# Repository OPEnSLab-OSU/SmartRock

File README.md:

# Smart Rock |<!-- [Updates](https://github.com/OPEnSLab-OSU/OPEnS-Lab-Home/wiki/smart-rock-updates) |--> [Wiki](https://github.com/OPEnSLab-OSU/SmartRock/wiki)
Project Leads: **Tyler Slaght**

Project Members; **Chris Milford**, **Owen Schwab**, **Max Emrich**

<!--Past Team Members **Annika Sundstorm** **Colin Hale-Brown**-->

Interested in the project? Email us at: slaghtt@oregonstate.edu

Smart Rock aims to be a low cost, high accuracy, easy to use in-situ water quality measuring device. Our
goal with Smart Rock is to create an open source, low cost, and technically accessible hydrological sensor
suite. The intended result of this work allows data to be collected throughout a watershed; even in varied
and/or harsh conditions to improve system wide watershed knowledge.
Smart Rock could be used as a learning tool for students, teachers, and other citizen scientists. The
device currently costs ˜$350 in materials and takes approximately 4-8 hours to assemble and program.

Comprehensive Build Guide -> https://github.com/OPEnSLab-OSU/SmartRock/blob/master/Documentation/SmartRock_Guide-compressed.pdf

Smart Rock Paper -> https://github.com/OPEnSLab-OSU/SmartRock/blob/master/Documentation/SmartRock_Paper.pdf

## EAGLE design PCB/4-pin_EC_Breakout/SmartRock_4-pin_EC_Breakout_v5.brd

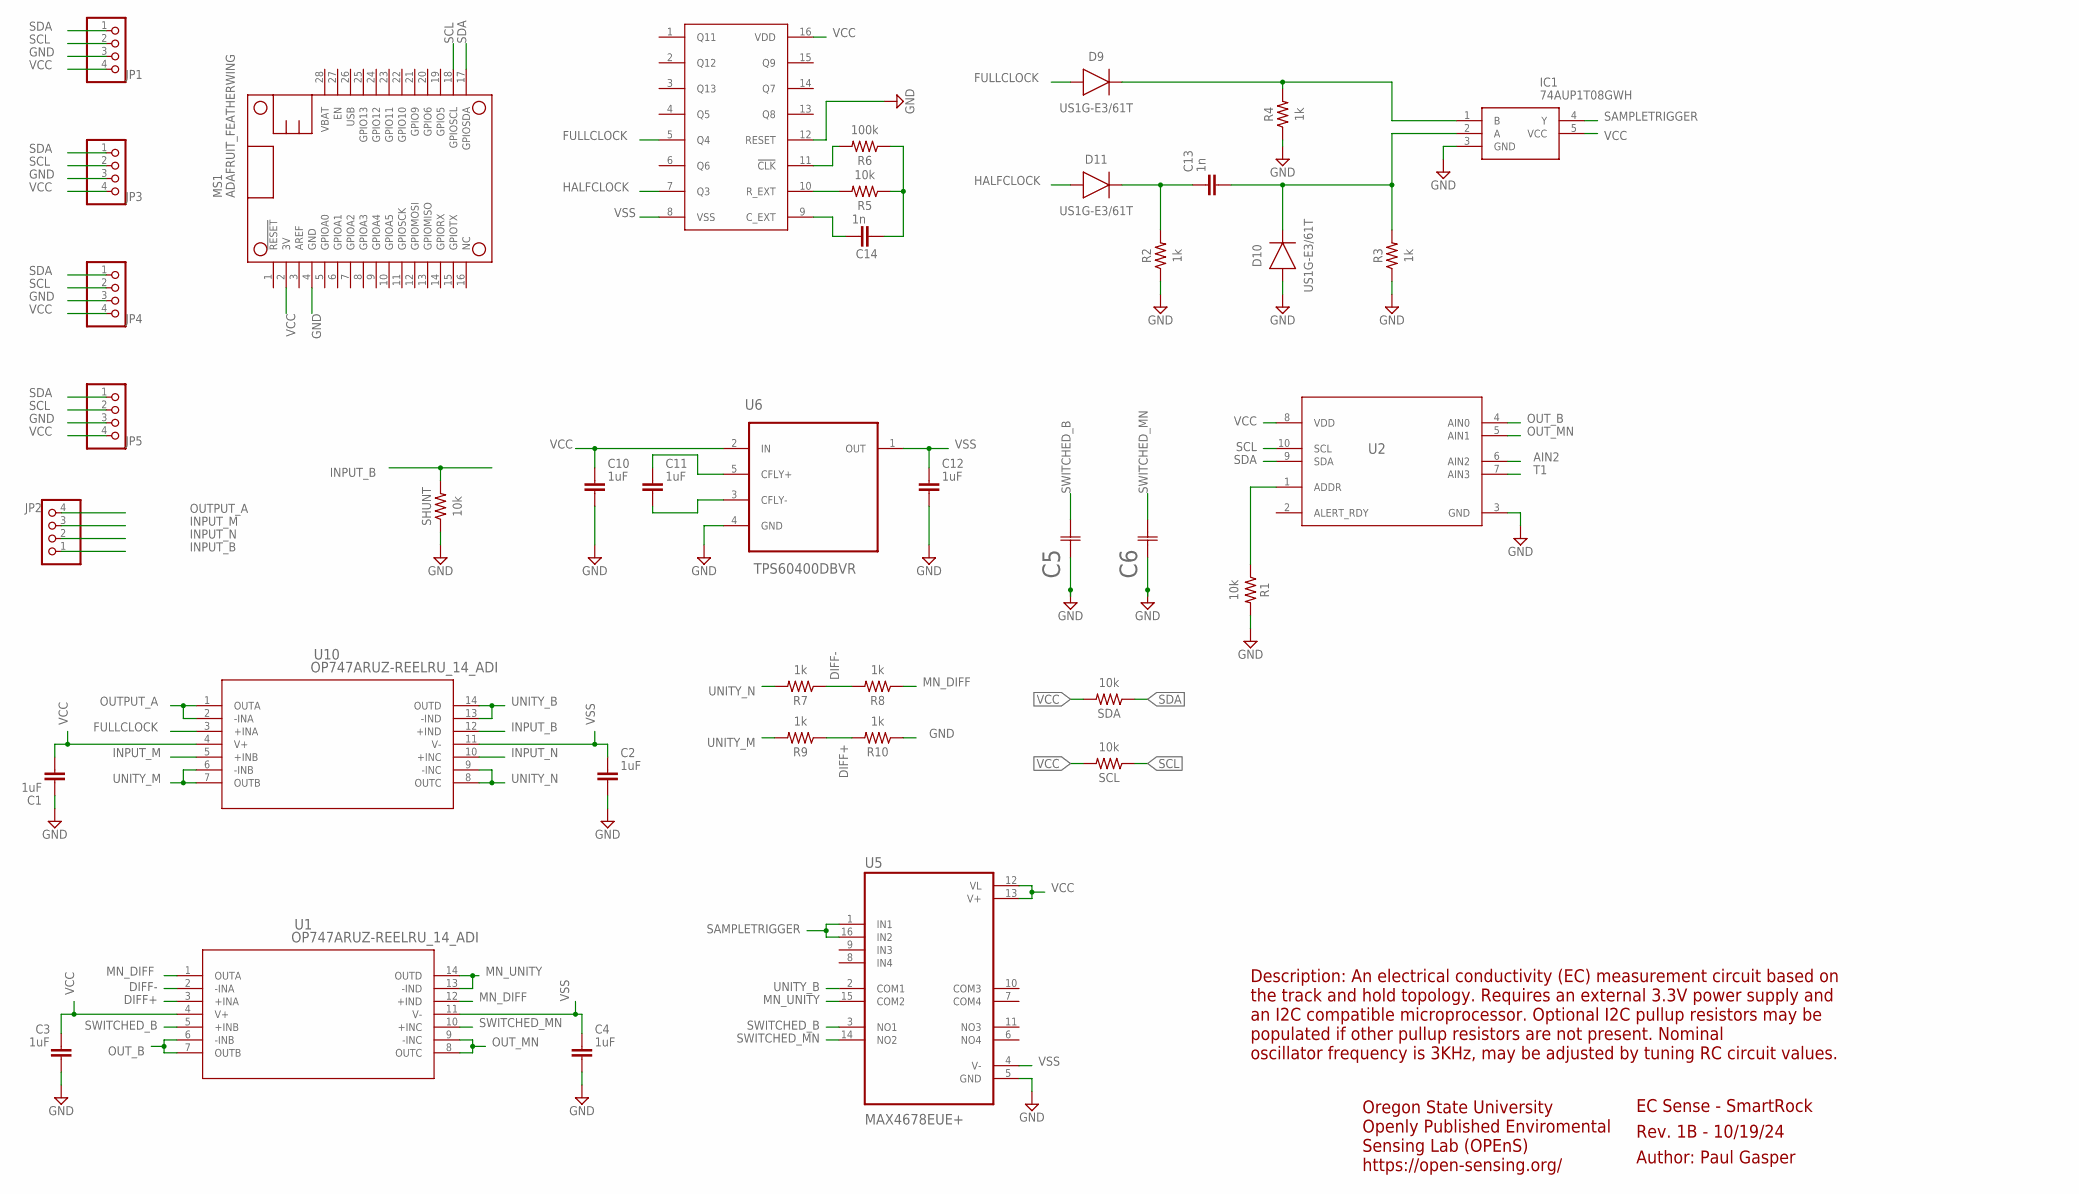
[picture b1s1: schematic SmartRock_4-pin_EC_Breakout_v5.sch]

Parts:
C1, C2, C3, C4, C10, C11, C12: 1uF; CAPC1005X60
C5, C6: 865090640004CAP_WCAP-ASLU_04P0X05P5_WRE-L; CAP_WCAP-ASLU_04P0X05P5_WRE-L
C13, C14: 1n; CAPC1005X60
D9, D10, D11: US1G-E3/61T; DIOM5226X290N
IC1: 74AUP1T08GWH; SOT65P212X110-5N
JP1, JP2, JP3, JP4, JP5: PINHD-1X4; 1X04
MS1: ADAFRUIT_FEATHERWING
R1, R5: 10k; RESC1005X40
R2, R3, R4, R7, R8, R9, R10: 1k; RESC1005X40
R6: 100k; RESC1005X40
SCL: 10k; RESC1005X40
SDA: 10k; RESC1005X40
SHUNT: 10k; RESC1005X40
U1, U10: OP747ARUZ-REELRU_14_ADI; RU_14_ADI
U2: ADS1115IDGSRDGS0010A_L; DGS0010A_L
U4: CD4060BPWR
U5: MAX4678EUE+; SOP65P640X110-16N
U6: TPS60400DBVR; SOT95P280X145-5N

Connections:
AIN2: U2.6 (AIN2)
DIFF+: R9.1, R10.2, U1.3 (+INA)
DIFF-: R7.1, R8.2, U1.2 (-INA)
FULLCLOCK: D9.2 (A), U4.5 (Q4), U10.3 (+INA)
GND: C1.1, C2.2, C3.2, C4.2, C5.1, C6.1, C10.2, C12.2, D10.2 (A), IC1.3 (GND), JP1.3, JP3.3, JP4.3, JP5.3, MS1.4 (GND), R1.2, R2.1, R3.1, R4.1, R10.1, SHUNT.1, U2.3 (GND), U4.12 (RESET), U5.5 (GND), U6.4 (GND)
HALFCLOCK: D11.2 (A), U4.7 (Q3)
INPUT_B: JP2.1, SHUNT.2, U10.12 (+IND)
INPUT_M: JP2.3, U10.5 (+INB)
INPUT_N: JP2.2, U10.10 (+INC)
MN_DIFF: R8.1, U1.1 (OUTA), U1.12 (+IND)
MN_UNITY: U1.13 (-IND), U1.14 (OUTD), U5.15 (COM2)
unnamed: D9.1 (C), IC1.1 (B), R4.2
unnamed: C13.1, D11.1 (C), R2.2
unnamed: C11.2, U6.3 (CFLY-)
unnamed: C11.1, U6.5 (CFLY+)
unnamed: C13.2, D10.1 (C), IC1.2 (A), R3.2
unnamed: R6.2, U4.11 (!CLK)
unnamed: R5.2, U4.10 (R_EXT)
unnamed: C14.1, U4.9 (C_EXT)
unnamed: C14.2, R5.1, R6.1
unnamed: R1.1, U2.1 (ADDR)
OUTPUT_A: JP2.4, U10.1 (OUTA), U10.2 (-INA)
OUT_B: U1.6 (-INB), U1.7 (OUTB), U2.4 (AIN0)
OUT_MN: U1.8 (OUTC), U1.9 (-INC), U2.5 (AIN1)
SAMPLETRIGGER: IC1.4 (Y), U5.1 (IN1), U5.16 (IN2)
SCL: JP1.2, JP3.2, JP4.2, JP5.2, MS1.18 (GPIOSCL), SCL.1, U2.10 (SCL)
SDA: JP1.1, JP3.1, JP4.1, JP5.1, MS1.17 (GPIOSDA), SDA.1, U2.9 (SDA)
SWITCHED_B: C5.2, U1.5 (+INB), U5.3 (NO1)
SWITCHED_MN: C6.2, U1.10 (+INC), U5.14 (NO2)
T1: U2.7 (AIN3)
UNITY_B: U5.2 (COM1), U10.13 (-IND), U10.14 (OUTD)
UNITY_M: R9.2, U10.6 (-INB), U10.7 (OUTB)
UNITY_N: R7.2, U10.8 (OUTC), U10.9 (-INC)
VCC: C1.2, C3.1, C10.1, IC1.5 (VCC), JP1.4, JP3.4, JP4.4, JP5.4, MS1.2 (3V), SCL.2, SDA.2, U1.4 (V+), U2.8 (VDD), U4.16 (VDD), U5.12 (VL), U5.13 (V+), U6.2 (IN), U10.4 (V+)
VSS: C2.1, C4.1, C12.1, U1.11 (V-), U4.8 (VSS), U5.4 (V-), U6.1 (OUT), U10.11 (V-)

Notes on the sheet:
EC Sense - SmartRock
Rev. 1B - 10/19/24
Author: Paul Gasper
Oregon State University Openly Published Enviromental Sensing Lab (OPEnS) https://open-sensing.org/
Description: An electrical conductivity (EC) measurement circuit based on the track and hold topology. Requires an external 3.3V power supply and an I2C compatible microprocessor. Optional I2C pullup resistors may be populated if other pullup resistors are not present. Nominal oscillator frequency 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

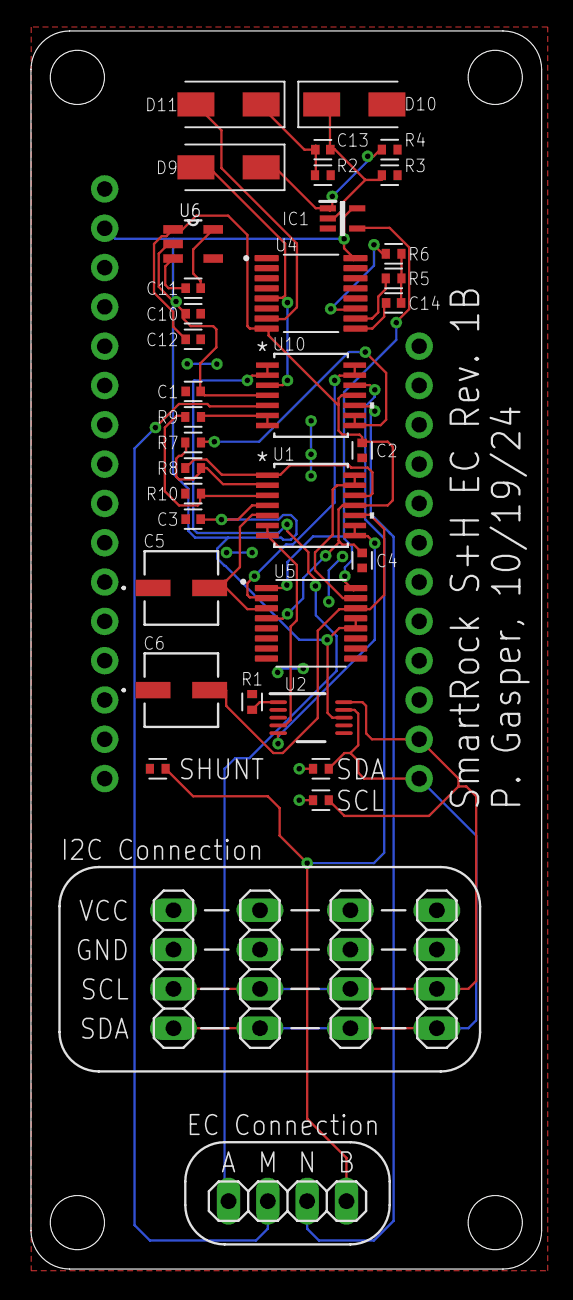
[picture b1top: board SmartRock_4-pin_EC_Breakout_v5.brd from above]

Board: 2 copper layers, 33.0 x 80.0 mm, 40 parts (0 on the bottom side), 33 nets.

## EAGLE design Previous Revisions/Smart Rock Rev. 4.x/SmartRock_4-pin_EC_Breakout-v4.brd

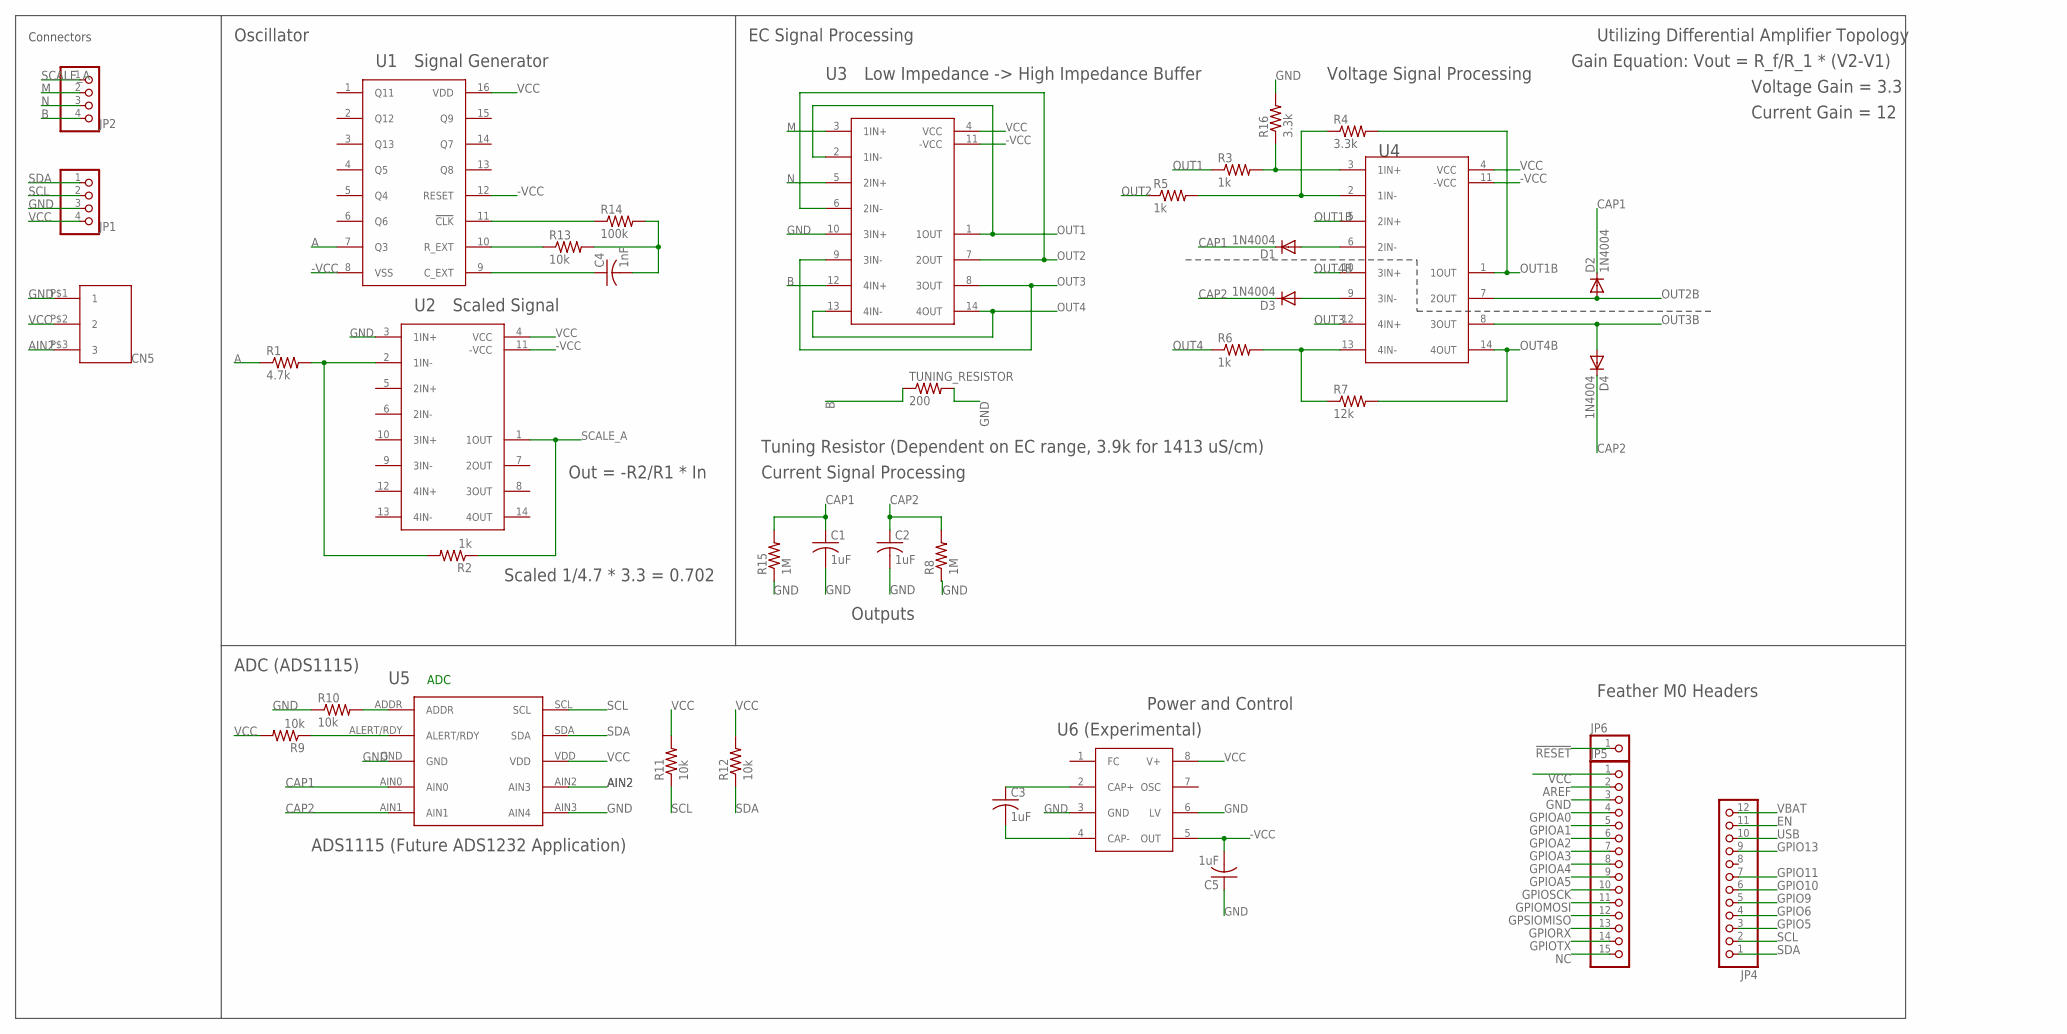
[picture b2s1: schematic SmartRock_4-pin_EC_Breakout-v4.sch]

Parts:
C1, C2, C3, C5: 1uF; C025-024X044
C4: 1nF; C1206
CN2: JST_3PIN_2MM
D1, D2, D3, D4: 1N4004; DO41-10
JP1, JP2: PINHD-1X4; 1X04
JP4: PINHD-1X12-CB; 1X12-CB
JP5: PINHD-1X15-CB; 1X15-CB
JP6: PINHD-1X1CB; 1X01-CLEANBIG
R1: 4.7k; M1206
R2, R3, R5, R6: 1k; M1206
R4, R16: 3.3k; M1206
R7: 12k; M1206
R8, R15: 1M; M1206
R9, R10, R11, R12, R13: 10k; M1206
R14: 100k; M1206
TUNING_RESISTOR: 200; M1206
U1: CD4060BPWR
U2, U3, U4: TL074CPWR; LT074CPWR
U5: ADS1115
U6+: MAX660MX/NOPB

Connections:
!RESET: JP6.1
-VCC: C5.2, U1.8 (VSS), U1.12 (RESET), U2.11 (-VCC), U3.11 (-VCC), U4.11 (-VCC), U6+.5 (OUT)
A: R1.1, U1.7 (Q3)
AIN2: CN2.P$3 (3), U5.AIN2 (AIN3)
AREF: JP5.2
B: JP2.4, TUNING_RESISTOR.1, U3.12 (4IN+)
CAP1: C1.1, D1.C, D2.C, R15.2, U5.AIN0
CAP2: C2.1, D3.C, D4.C, R8.2, U5.AIN1
EN: JP4.11
GND: C1.2, C2.2, C5.1, CN2.P$1 (1), JP1.3, JP5.3, R8.1, R10.1, R15.1, R16.2, TUNING_RESISTOR.2, U2.3 (1IN+), U3.10 (3IN+), U5.AIN3 (AIN4), U5.GND, U6+.3 (GND), U6+.6 (LV)
GPIO5: JP4.3
GPIO6: JP4.4
GPIO9: JP4.5
GPIO10: JP4.6
GPIO11: JP4.7
GPIO13: JP4.9
GPIOA0: JP5.4
GPIOA1: JP5.5
GPIOA2: JP5.6
GPIOA3: JP5.7
GPIOA4: JP5.8
GPIOA5: JP5.9
GPIOMOSI: JP5.11
GPIORX: JP5.13
GPIOSCK: JP5.10
GPIOTX: JP5.14
GPSIOMISO: JP5.12
M: JP2.2, U3.3 (1IN+)
N: JP2.3, U3.5 (2IN+)
unnamed: R3.2, R16.1, U4.3 (1IN+)
unnamed: R4.1, R5.2, U4.2 (1IN-)
unnamed: R1.2, R2.2, U2.2 (1IN-)
unnamed: D1.A, U4.6 (2IN-)
unnamed: R6.2, R7.1, U4.13 (4IN-)
unnamed: D3.A, U4.9 (3IN-)
unnamed: C3.1, U6+.2 (CAP+)
unnamed: C3.2, U6+.4 (CAP-)
unnamed: C4.1, U1.9 (C_EXT)
unnamed: R13.1, U1.10 (R_EXT)
unnamed: R14.1, U1.11 (!CLK)
unnamed: R10.2, U5.ADDR
unnamed: R9.1, U5.ALERT/RDY
unnamed: C4.2, R13.2, R14.2
NC: JP5.15
OUT1: R3.1, U3.1 (1OUT), U3.2 (1IN-)
OUT1B: R4.2, U4.1 (1OUT), U4.5 (2IN+)
OUT2: R5.1, U3.6 (2IN-), U3.7 (2OUT)
OUT2B: D2.A, U4.7 (2OUT)
OUT3: U3.8 (3OUT), U3.9 (3IN-), U4.12 (4IN+)
OUT3B: D4.A, U4.8 (3OUT)
OUT4: R6.1, U3.13 (4IN-), U3.14 (4OUT)
OUT4B: R7.2, U4.10 (3IN+), U4.14 (4OUT)
SCALE_A: JP2.1, R2.1, U2.1 (1OUT)
SCL: JP1.2, JP4.2, R11.1, U5.SCL
SDA: JP1.1, JP4.1, R12.1, U5.SDA
USB: JP4.10
VBAT: JP4.12
VCC: CN2.P$2 (2), JP1.4, JP5.1, R9.2, R11.2, R12.2, U1.16 (VDD), U2.4 (VCC), U3.4 (VCC), U4.4 (VCC), U5.VDD, U6+.8 (V+)

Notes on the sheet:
Oscillator
ADC (ADS1115)
Power and Control
ADC
Connectors
EC Signal Processing
Signal Generator
Scaled Signal
Out = -R2/R1 * In
Scaled 1/4.7 * 3.3 = 0.702
Low Impedance -> High Impedance Buffer
Voltage Signal Processing
Current Signal Processing
Outputs
Tuning Resistor (Dependent on EC range, 3.9k for 1413 uS/cm)
Utilizing Differential Amplifier Topology
Gain Equation: Vout = R_f/R_1 * (V2-V1)
Voltage Gain = 3.3
Current Gain = 12
ADS1115 (Future ADS1232 Application)
Feather M0 Headers
U6 (Experimental)
CN5

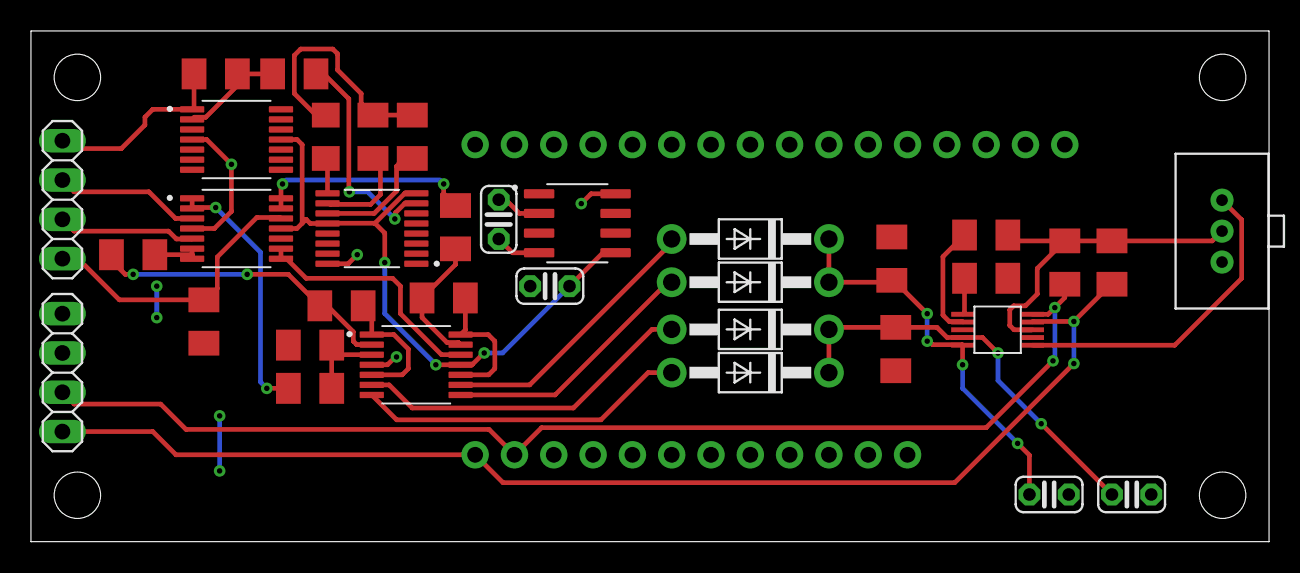
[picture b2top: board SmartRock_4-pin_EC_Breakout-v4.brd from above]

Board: 2 copper layers, 80.0 x 33.0 mm, 38 parts (0 on the bottom side), 35 nets.

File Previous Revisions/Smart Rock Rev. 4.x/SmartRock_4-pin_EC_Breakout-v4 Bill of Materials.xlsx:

EAGLE Board # | Part | Part Number | Footprint/Package | Quantity/Board | Source (Link)
U2,U3,U4 | Quad OPAMP IC | TL074CPWR | 14TSSOP | 3.0 | Digikey
U1 | Binary Counter IC | CD4060BPWR | 16TSSOP | 1.0 | Digikey
U5 | 16 bit ADC IC | ADS1115BQDGSRQ1 | 10VSSOP | 1.0 | Digikey
U6+ | Charge Pump Inverter IC | MAX660MX/NOPB | 8SOIC | 1.0 | Digikey
C1,C2 | 1 uF Electrolytic Cap | UPS1H010MDD1TD | Radial, Can (though hole) | 2.0 | Digikey
C3, C5 | 100 uF Electrolytic Cap | 10YXF100MEFCT15X11 | Radial, Can (though hole) | 2.0 | Digikey
C4 | 1 nF Ceramic Cap | 1206GC102KAT2A | 1206 (3216 metric) SMD | 1.0 | Digikey
C8,C9,C10 | 1 uF Ceramic Cap | C1206C105K5REC7210 | 1206 (3216 metric) SMD | 3.0 | Digikey
D1,D2,D3,D4 | 1N4001 Diode | 1N4001-G | DO-204AL, DO-41, Axial (through hole) | 4.0 | Digikey
R2, R3, R5, R6 | 1k ohm resistor 1% | RC1206FR-071KL | 1206 (3216 metric) SMD | 4.0 | Digikey
R1, R4, R16 | 3.3k ohm resistor 1% | RC1206FR-073K3L | 1206 (3216 metric) SMD | 3.0 | Digikey
R8, R15 | 1M ohm resistor 1% | RC1206FR-071ML | 1206 (3216 metric) SMD | 2.0 | Digikey
R7, R9, R10, R11, R12, R13 | 10k ohm resistor 1% | RC1206FR-0710KL | 1206 (3216 metric) SMD | 6.0 | Digikey
R14 | 100k ohm resistor 1% | RC1206FR-07100KL | 1206 (3216 metric) SMD | 1.0 | Digikey
TUNING_RESISTOR | 200 ohm resistor 1% | RC1206FR-07200RL | 1206 (3216 metric) SMD | 1.0 | Digikey

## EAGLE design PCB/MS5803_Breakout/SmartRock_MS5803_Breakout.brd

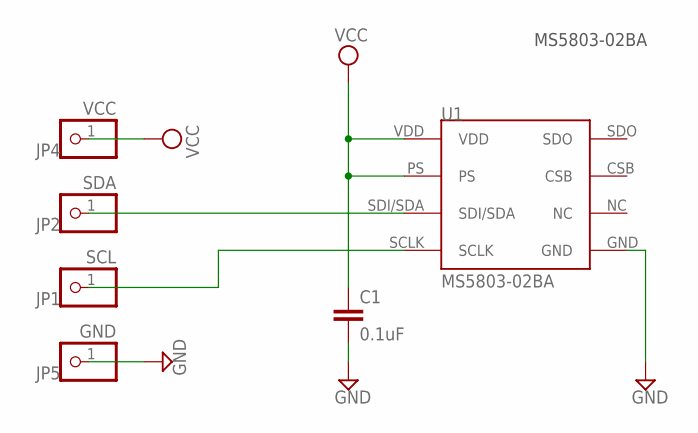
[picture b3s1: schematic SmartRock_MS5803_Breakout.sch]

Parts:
C1: 0.1uF; C0805
JP1: SCL; 1X01
JP2: SDA; 1X01
JP4: VCC; 1X01
JP5: GND; 1X01
U1: MS5803-02BA

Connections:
GND: C1.2, JP5.1, U1.GND
unnamed: JP2.1, U1.SDI/SDA
unnamed: JP1.1, U1.SCLK
VCC: C1.1, JP4.1, U1.PS, U1.VDD

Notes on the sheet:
MS5803-02BA

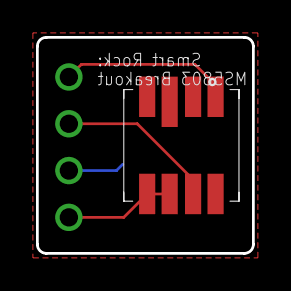
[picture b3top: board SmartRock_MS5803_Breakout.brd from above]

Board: 2 copper layers, 12.0 x 12.0 mm, 6 parts (1 on the bottom side), 4 nets.

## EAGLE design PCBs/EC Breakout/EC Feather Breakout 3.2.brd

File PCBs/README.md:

# Custom PCBs

Each Smart Rock contains three custom PCBs, the EC breakout board and OsmoPod can be found here. Information about the Hypnos Board can be found [Here](https://github.com/OPEnSLab-OSU/OPEnS-Lab-Home/wiki/Hypnos).

Board | Description
----- | -----
EC Breakout	| Module containing EC circuitry and breakout plugs for the other sensors.
OsmoPod | Module containing EC probes and MS5803 pressure/ temperature sensor.
Hypnos | Module for time, sleep, and data storage functionalities of the Smart Rock.

Please referance the correct PCB for your Smart Rock, board verions have changed as we have shipped.

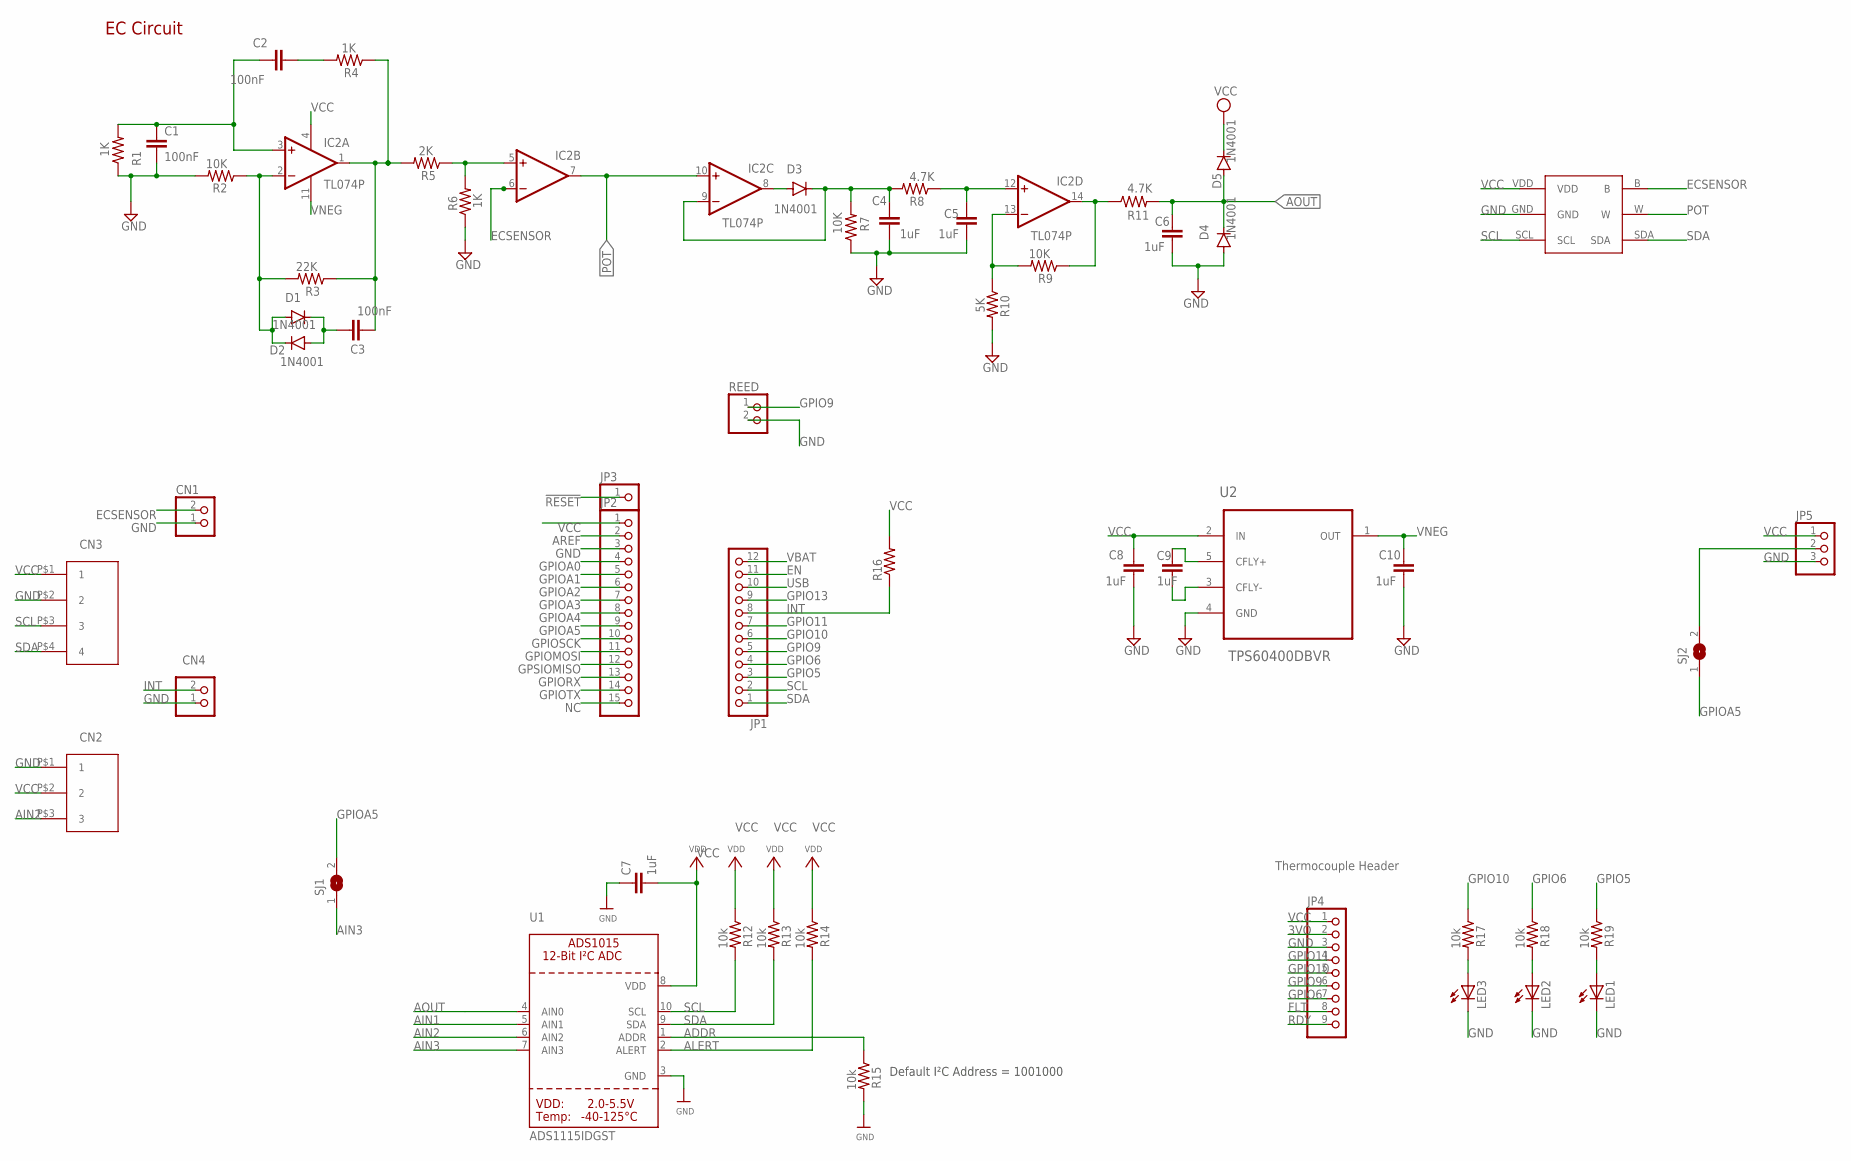
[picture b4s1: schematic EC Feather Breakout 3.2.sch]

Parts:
C1, C2, C3: 100nF; C1206
C4, C5, C6, C7, C8, C9, C10: 1uF; C1206
CN1, CN4: JST_2PIN-THM; JST-PH-2-THM
D1, D2, D3, D4, D5: 1N4001; D-5
IC2: TL074P; DIL14
JP1: PINHD-1X12-CB; 1X12-CB
JP2: PINHD-1X15-CB; 1X15-CB
JP3: PINHD-1X1CB; 1X01-CLEANBIG
JP4: PINHD-1X9; 1X09
JP5: PINHD-1X3CB; 1X03-CLEANBIG
LED1, LED2, LED3: LEDSMT1206; 1206
R1, R4, R6: 1K; R1206
R2, R7, R9: 10K; R1206
R3: 22K; R1206
R5: 2K; R1206
R8, R11: 4.7K; R1206
R10: 5K; R1206
R12, R13, R14, R15, R17, R18, R19: 10k; R1206
R16: R-US_M1206; M1206
REED: PINHD-1X2; 1X02
SJ1, SJ2: SJ
U1: ADS1115IDGST; MSOP10
U2: TPS60400DBVR; SOT95P280X145-5N
U$1: AD5246
U$7: JST_4PIN_2MM
U$9: JST_3PIN_2MM

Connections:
3VO: JP4.2
!RESET: JP3.1
ADDR: R15.1, U1.1 (ADDR)
AIN1: U1.5 (AIN1)
AIN2: U1.6 (AIN2), U$9.P$3 (3)
AIN3: SJ1.1, U1.7 (AIN3)
ALERT: R14.2, U1.2 (ALERT)
AOUT: C6.2, D4.C, D5.A, R11.2, U1.4 (AIN0)
AREF: JP2.2
ECSENSOR: CN1.2 (1), IC2.6 (-IN), U$1.B
EN: JP1.11
FLT: JP4.8
GND: C1.2, C4.1, C5.1, C6.1, C7.1, C8.1, C10.1, CN1.1 (2), CN4.1 (2), D4.A, JP2.3, JP4.3, JP5.3, LED1.C, LED2.C, LED3.C, R1.1, R2.2, R6.1, R7.1, R10.2, R15.2, REED.2, U1.3 (GND), U2.4 (GND), U$1.GND, U$7.P$2 (2), U$9.P$1 (1)
GPIO5: JP1.3, R19.1
GPIO6: JP1.4, JP4.7, R18.1
GPIO9: JP1.5, JP4.6, REED.1
GPIO10: JP1.6, JP4.5, R17.1
GPIO11: JP1.7, JP4.4
GPIO13: JP1.9
GPIOA0: JP2.4
GPIOA1: JP2.5
GPIOA2: JP2.6
GPIOA3: JP2.7
GPIOA4: JP2.8
GPIOA5: JP2.9, SJ1.2, SJ2.1
GPIOMOSI: JP2.11
GPIORX: JP2.13
GPIOSCK: JP2.10
GPIOTX: JP2.14
GPSIOMISO: JP2.12
INT: CN4.2 (1), JP1.8, R16.1
unnamed: C1.1, C2.1, IC2.3 (+IN), R1.2
unnamed: C2.2, R4.2
unnamed: C3.2, IC2.1 (OUT), R3.1, R4.1, R5.2
unnamed: D1.A, D2.C, IC2.2 (-IN), R2.1, R3.2
unnamed: IC2.5 (+IN), R5.1, R6.2
unnamed: JP5.2, SJ2.2
unnamed: C3.1, D1.C, D2.A
unnamed: C4.2, D3.C, IC2.9 (-IN), R7.2, R8.2
unnamed: D3.A, IC2.8 (OUT)
unnamed: C5.2, IC2.12 (+IN), R8.1
unnamed: IC2.13 (-IN), R9.2, R10.1
unnamed: IC2.14 (OUT), R9.1, R11.1
unnamed: LED3.A, R17.2
unnamed: LED2.A, R18.2
unnamed: LED1.A, R19.2
unnamed: C9.2, U2.5 (CFLY+)
unnamed: C9.1, U2.3 (CFLY-)
NC: JP2.15
POT: IC2.7 (OUT), IC2.10 (+IN), U$1.W
RDY: JP4.9
SCL: JP1.2, R12.2, U1.10 (SCL), U$1.SCL, U$7.P$3 (3)
SDA: JP1.1, R13.2, U1.9 (SDA), U$1.SDA, U$7.P$4 (4)
USB: JP1.10
VBAT: JP1.12
VCC: C7.2, C8.2, D5.C, IC2.4 (V+), JP2.1, JP4.1, JP5.1, R12.1, R13.1, R14.1, R16.2, U1.8 (VDD), U2.2 (IN), U$1.VDD, U$7.P$1 (1), U$9.P$2 (2)
VNEG: C10.2, IC2.11 (V-), U2.1 (OUT)

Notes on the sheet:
EC Circuit
Default I²C Address = 1001000
CN4
CN2
CN3
Thermocouple Header

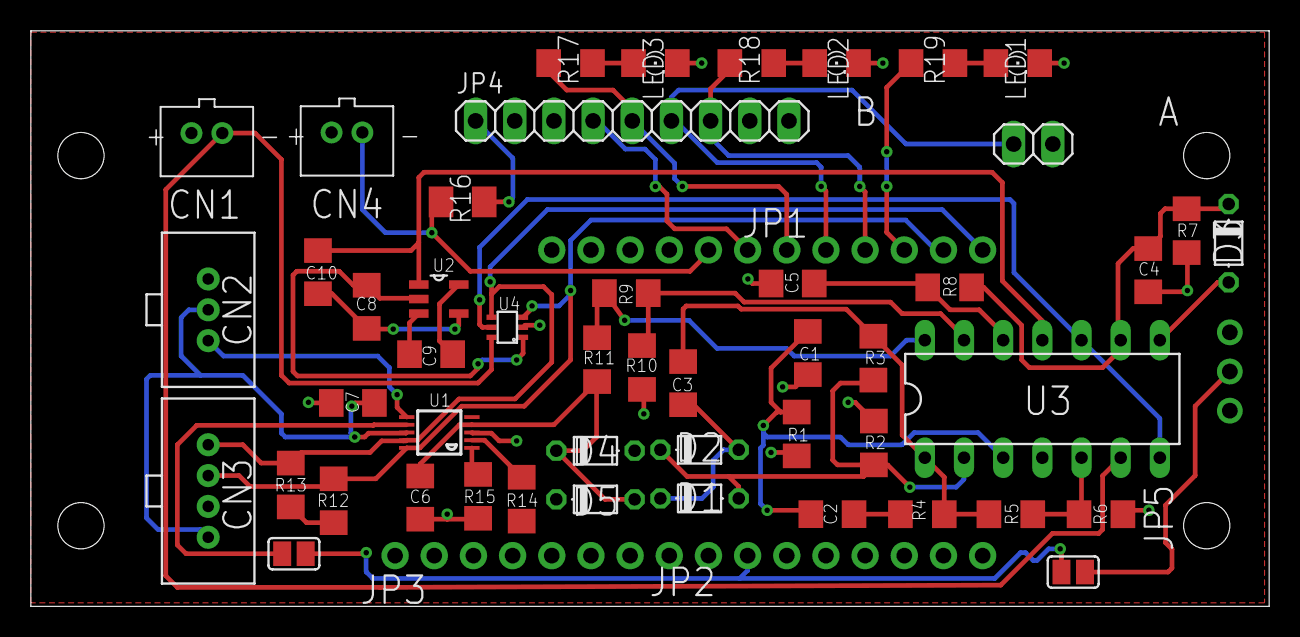
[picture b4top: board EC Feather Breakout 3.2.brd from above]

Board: 2 copper layers, 80.3 x 37.3 mm, 53 parts (0 on the bottom side), 36 nets.

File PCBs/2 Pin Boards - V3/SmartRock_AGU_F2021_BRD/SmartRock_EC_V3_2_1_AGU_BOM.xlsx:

Board Label | Value | Item Description | Quantity Given | Quantity per Device | Cost per Unit | Cost per Device | Product Site | Manufacturer ID | Packaging/Case | Type | Notes | Alternative Source
JP1 | 12 Pin (Female) | CONN HDR 12POS 0.1 TIN PCB | 1 | 1 | 0.78 |  | Digikey | S6100-ND | Tray
JP2 + JP3 | 16 Pin (Female) | CONN HDR 16POS 0.1 TIN PCB | 1 | 1 | 0.98 |  | Digikey | S7014-ND | Tray
JP5 | 3 Pin (Male) | CONN HEADER VERT 3POS 2.54MM | 1 | 1 | 0.13 |  | Digikey | 732-5316-ND | Tray |  | OOS
CN1 | 2 Pin 2.5mm JST | CONN HEADER VERT 2POS 2MM | 1 | 1 | 0.17 |  | Digikey | 455-1704-ND | Bulk |  | OOS
CN2 | 3 Pin 2.5mm JST | CONN HEADER VERT 3POS 2MM | 1 | 1 | 0.19 |  | Digikey | 455-1705-ND | Bulk |  | OOS
CN3 | 4 Pin 2.5mm JST | CONN HEADER VERT 4POS 2MM | 1 | 1 | 0.24 |  | Digikey | 455-1706-ND | Bulk |  | OOS
U1 | ADS1115 | IC ADC 16BIT SIGMA-DELTA 10VSSOP | 1 | 1 | 6.38 |  | Digikey | IC ADC 16BIT SIGMA-DELTA 10VSSOP | Cut Tape/VSSOP |  | OOS
U2 | 3.3V Inverter | IC REG CHARG PUMP INV 60MA SOT23 | 1 | 1 | 1.1399999999999999 |  | Digikey | 296-27004-1-ND - Cut Tape | Cut Tape/SOT-753 |  | OOS
U3 | Op-Amp | IC OPAMP JFET 4 CIRCUIT 14DIP | 1 | 1 | 0.85 |  | Digikey | 296-1777-ND | Tube/14-PDIP |  | OOS
S1 | SPDT Switch | SWITCH SLIDE SPDT 200MA 30V | 1 | 1 | 0.76 |  | Digikey | EG1903-ND | Bulk
D1,D2,D3,D4,D5 | 1N4001 Diodes |  |  |  |  |  |  |  |  |  | Good to Go
C1,C2,C3 | 100nF
C4,C5,C6,C7,C8,C9,C10 | 1uF
R1,R4,R6,R17 | 1k |  |  |  |  |  | Digikey |  |  |  | Already Thick Film
R5 | 2k |  |  |  |  |  | Digikey |  |  |  | Already Thick Film
R8,R11,R18,R19 | 4.7k |  |  |  |  |  | Digikey |  |  |  | Already Thick Film
R10 | 5k(4.99k) |  |  |  |  |  | Digikey |  |  |  | Updated to Thick Film
R2,R7,R9,R14,R15 | 10k |  |  |  |  |  |  |  |  |  | Already Thick Film
R3 | 22k |  |  |  |  |  |  |  |  |  | Already Thick Film
LED1,LED2,LED3

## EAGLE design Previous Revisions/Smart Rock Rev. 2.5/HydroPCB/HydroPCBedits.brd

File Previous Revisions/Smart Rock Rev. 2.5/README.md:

# Smart Rock | [Updates](https://github.com/OPEnSLab-OSU/OPEnS-Lab-Home/wiki/smart-rock-updates) | [Github](https://github.com/OPEnSLab-OSU/SmartRock)
Project Leads: **Alicia Veach**, **Martin Escoto**, and **Colin Hale-Brown**

Interest in the project? Email us at: halebroc@oregonstate.edu

## Overview
Current hydrological modelling is missing data from small and seasonal streams. Data collection on these streams is sparse with measurements, if any data is taken at all. Small streams are often ignored in hydrological modelling by entities that generate public data of water resources. The ecological health of habitats for fish depends on the flow of these small streams during different seasons. monitoring can be expensive and exclusive to organizations that can afford to do so. Current barriers prevent current hydrological modeling being informed by small and seasonal streams. 

Smart Rock aims to create a low-cost device to monitor remote streams through citizen science. The device could be used as a learning tool for students, teachers, and other citizen scientists. Deploying Smart Rock in streams will allow for more accurate data collection of small and seasonal streams.

<!--- {{:20190427_164150.jpg?400|}} -->
## Description

The Smart Rock is a submersible sensor suite that monitors water depth, temperature, turbidity, and salinity (EC) of a small stream over time and designed to be built by anyone with or without extensive experience in electronics.
Current capabilities of Smart Rock sensors are depth measurement with accuracy within 0.13 mbar resolution as compared to an out of water pressure sensor, temperature accuracy of fewer than 0.01°C, turbidity measured in JTU, and a salinity measurement that increases accuracy to less than 5 parts per million. Battery life for Smart Rock is up to 3 months with low power sleep, a function that limits power usage from the device when dormant. This can be extended by taking data less often than once every 20 minutes. The device currently costs ~ $200 with these specifications and custom parts and takes about 10 hours to assemble and program.

**Adafruit Feather M0 Basic Proto**

<details>
<summary>Show More</summary>

General Description/how it works:
	The Feather M0 Basic Proto is an Arduino-compatible microcontroller that runs on 3.3 volts. A 3.3 volt regulator allows for a 3.7 volt lithium polymer battery to be used. The feather has a 500mA peak current, has 20 GPIO pins, 10 analog inputs, and 1 analog output. These pins allow users to connect their sensors and motors to the controller to program readability and functions with Arduino.

Smart Rock Use Validation:
	The Feather M0 Basic Proto acts as the main microcontroller for Smart Rock. Integrated into the PCB, the feather gives inputs to sensors and other electronics and reads outputs. Sensors operate on the I2C interface and analog inputs. The Feather saves data to SD in a spreadsheet from the stream on Hypnos.
</details>

**Pressure/Temperature Sensor**

<details>
<summary>Show More</summary>

General Description/how it works: 
The pressure sensor runs on 3 volts from a microcontroller or direct source. The MS5803 Pressure sensor uses piezoresistivity to output pressure readings. Piezoresistivity is the change in electrical resistivity of a semiconductor when mechanical strain is applied. The sensor converts an analog output into a 24 digit output that runs on the I2C protocol. The sensor additionally provides a 24 digit output for temperature. The sensor has been calibrated at 2 temperatures and 2 pressures and 6 coefficients are calculated and stored in a 128-bit PROM. When taking new readings, the device first reads this calibration data. The digital pressure data (D1) and digital temperature data (D2) are read and temperature and pressure are then calculated. Temperature is calculated in two steps: subtracting the read temperature from the reference temperature and comparing to the temperature coefficient from calibration. Then, the electrical sensitivity is read and the actual temperature calculation is used in another calculation regarding the pressure offset caused by temperature. Following I2C protocol communication, SDA (Serial Data) output conveys the pressure and temperature readings to a microcontroller.

Smart Rock Use Validation:
	The pressure and temperature gives a two for one. Costing $10.72, this sensor provides the two primary measurements we need with one sensor. Measuring temperature and depth of a stream are the most useful in determining basic data about a remote and unknown stream. With a custom PCB designed for this sensor, connecting the sensor to the microcontroller is made easier. Following I2C protocol, the sensor is already implemented into LOOM_Library. This allows for the programming of the system to be simple. The sensor gives accurate and useful data within our budget. The size of the sensor is also fairly small and easy to make water proof.

</details>

**Turbidity Sensor**

<details>
<summary>Show More</summary>

General Description/ How it works:
	Turbidity is the measurement of the cloudiness in a liquid. This sensor uses a measurement of light transmittance to determined the total suspended solids (TSS) in the liquid. TSS increases with turbidity. Turbidity is measured in JTU which can be used to determine the cleanliness of the water, water erosion, and pollution. The sensor gives an analog output that can be converted to a measurement in JTU. Using a laser signal between two nodes, the device can convert cloudiness to JTU.

Smart Rock Use Validation:
	Turbidity in a stream can indicate the overall quality of the water and gives an idea for the amount of erosion occurring. Adding this sensor to the Smart Rock is both cheap and simple. The sensor from DF Robot costs $9.90, making it easy to keep Smart Rock inexpensive. The sensor can be hooked up to the Smart Rock through three easy connections, 3V power, GND, and an analog port. Implementing the sensor board to the electronics is relatively simple because it comes with a PCB that can be wired to the Smart Rock base PCB.

</details>

**Salinity Sensor**

<details>
<summary>Show More</summary>

General Description/How it works:
	TDS measures the amount of organic and inorganic dissolved solids in the liquid. Using electrical conductivity, the sensor gives an analog reading that corresponds to the amount of minerals in the water. The sensor has two probes and the interference between them changes the voltage and an analog reading can be taken. The sensor kit comes with its own PCB, the electrical conductivity probe, and the required connectors.

Smart Rock Use Validation:
	Having a salinity measurement on the Smart Rock is cost effective and important to proving the capability of the sensor package. Electrical conductivity gives an idea to the amount of salts and minerals in the stream and can be used to determine the overall health of the stream. With this sensor costing $12.90, much less than similar probes, the price of having this on the Smart Rock is low enough to implement. The size of the probe is fairly small and can be sealed to be waterproof easily.
</details>

**OPEnS Lab Hypnos**

<details>
<summary>Show More</summary>

General Description/ How it works:
	The Hypnos board is an attachable precision I2C integrated real time clock and data logger. A crystal is used to keep time and is temperature compensated inside the chip. A coin cell battery is plugged into the board to keep time even when the a feather battery is not connected. Data can be saved and read from SPI or I2C protocol communication.

Smart Rock Use Validation:
	The Smart Rock is using the Hypnos to keep temperature compensated time as well as storing all the data read by the sensors while in the stream bed. Smart Rock takes data every 10 minutes and this device allows such to happen. The RTC sends a square wave signal to a digital pin on the feather to wake the device from the power sleep to take data. Having this RTC allows for the device to keep time even in a low-power sleep mode.

More information about the Hypnos Board can be found [here](https://github.com/OPEnSLab-OSU/OPEnS-Lab-Home/wiki/Hypnos).
</details>

<!--
**Reed Switch**

<details>
<summary>Show More</summary>

General Description/ How it works:
	A reed switch is a small device that closes/open when interacting with a magnetic field. It can be used for keeping a device off until opened, for example, a laptop screen. Always open reed switches remain open until a magnet is nearby. Then, it closes and allows current to flow through as a closed wire. Inside the switch there are two wires that are separated and held within a plastic frame. When a magnet is near, the two wire touch and allow current to flow.

Smart Rock Use Validation:
	The always open Reed switch for the Smart Rock is used as an interrupt. The device remains asleep until a user interacts with it with a magnet. The device can then wake and collect data to be transferred. The reed switch allows the battery to be saved by keeping the device off until it is used to collect and transfer data. The switch costs $1.08 for one, cheap and easy to implement. With LOOM, an interrupt can be easily added to wake the device when current flows from the ground to a desired pin, when the reed switch is closed.
</details>

**pH Sensor**

<details>
<summary>Show More</summary>

General Description/ How it works:
 pH is the measurement of hydrogen in a solution. This indicates the acidity of the water which is useful for the biological systems impacted by the stream. This pH sensor uses a pH composite electrode that gives a reading in millivolts that can be converted directly to pH using an analog reading. When calibrated, this probe has accuracy of +_ 0.1pH. 

Smart Rock Use Validation: 
This pH probe from DF robot comes with a pcb and the probe in standard solution. Although this probe is a lab grade probe and not meant for long-term submersion, this probe costs $29.50 and can give a good short term estimate of stream pH. Other probes tend to cost much more and are too bulky for the Smart Rock application. Having an estimate of pH can give information about the biological health of a stream. This pH sensor is also implemented into LOOM.

</details>
-->

### Casing Design

The **outer Case** is made of a piece of PVC with union fittings attached to either end. The union fittings are mounted to the PVC using a layer of primer, then a layer of PVC cement. The smaller diameter, unthreaded, section of the union fitting is discarded and replaced with a circular piece of acrylic. This piece of acrylic has laser-cut holes for the sensors to be epoxied to make water-tight. The o-ring in the union fitting is coated in silicone grease to ensure a waterproof seal when the end of the union fitting is screwed back on with the acrylic. This modded union fitting design is used so that the electronics may be accessed and so that we can have the sensors protruding from one end without getting their wires twisted and tangled when the end is removed. 

_*Note that the image above does not include full electronics or official electronics layout._

The **internal Structure** is made up of a 3D printed rail and an acrylic platform. One section of the rail is glued to the inside of the PVC, the other section is glued to a length of acrylic. The electronics are then mounted using velcro to this acrylic and slide into the case using the rail system. Using the rail and acrylic slide makes it easy to remove/access the electronics and holds everything in place. The electronics stack up on the slide allowing for a compact design

_*Note that the image above does not include full electronics or official electronics layout._

## Objectives

### Overall Targets:

*  Low cost

*  Durable

### Electrical Function Targets:
<details>
<summary>Show More</summary>

*  Senses underwater pressure for depth

*  Senses stream temperature

*  Senses turbidity

*  Senses salinity

*  Battery life of at least 1 week

*  Clean and user-friendly electronics packaging

*  Keeps time for data collections

*  Connects to user easily
</details>

### Casing Function Targets:
<details>
<summary>Show More</summary>

*  Waterproof

*  Remains in the location of placement

*  Electronics are securely mounted

*  Simple design

*  Aesthetically pleasing

*  Safe for the environment

*  Withstand freezing temperatures

*  Easy internal access

*  Easy to retrieve and transport
</details>

## Outcomes

Current capabilities of Smart Rock sensors are depth measurement with accuracy within 0.13 mbar resolution as compared to an out of water pressure sensor, temperature accuracy of fewer than 0.01°C, turbidity measured in JTU, and a salinity measurement with an accuracy of less than 5 parts per million. Future developments will have <!--pH sensing and--> flow sensing from the use of multiple high-accuracy pressure sensors. Battery life for Smart Rock is up to 3 months with low power sleep, a function that limits power usage from the device when dormant. This can be extended by taking data less often than once every 20 minutes. The device currently costs ~ $200 with these specifications and custom parts and takes about 10 hours to assemble and program.

### Field Test January 2020

## Future

Updating the Smart Rock to improve reliability and ease of use. Simplifying electronics so that the salinity sensor board is built into the main feather breakout and replacing all the dupont wires and standardizing to JST connectors to make assembly straightforward and user-friendly.
 
Preparing for CUAHSI workshop in summer 2020.

## Resource List

The Bill of Materials for the current iteration of the Smart Rock can be found [here](https://github.com/OPEnSLab-OSU/SmartRock/blob/master/Smart%20Rock%20Rev%202.5%20Bill%20of%20Materials%20for%20GitHub.xlsx).

Link to Github page with code and PCB design files can be found [here](https://github.com/OPEnSLab-OSU/SmartRock).

### Tutorials

Here are Resources from the 2019 CUAHSI workshop can be found [here](https://github.com/OPEnSLab-OSU/SmartRock/tree/master/Workshop%20Materials)

## Key Words
OPEnS, SmartRock, Smart Rock, Feather M0, Adalogger, Arduino, Stream, Water Monitor, Hydrological Data, Hydrological Monitoring, Pressure, Temperature, Electrical Conductivity, Dissolved Solids, Turbidity, pH, seasonal streams, small streams

## References

Software

*  Fusion 360. (2018). San Rafael, California: Autodesk.

*  EAGLE CAD. (2018). San Rafael, California: Autodesk.

*  Arduino IDE. (2020). Turin, Italy: Arduino

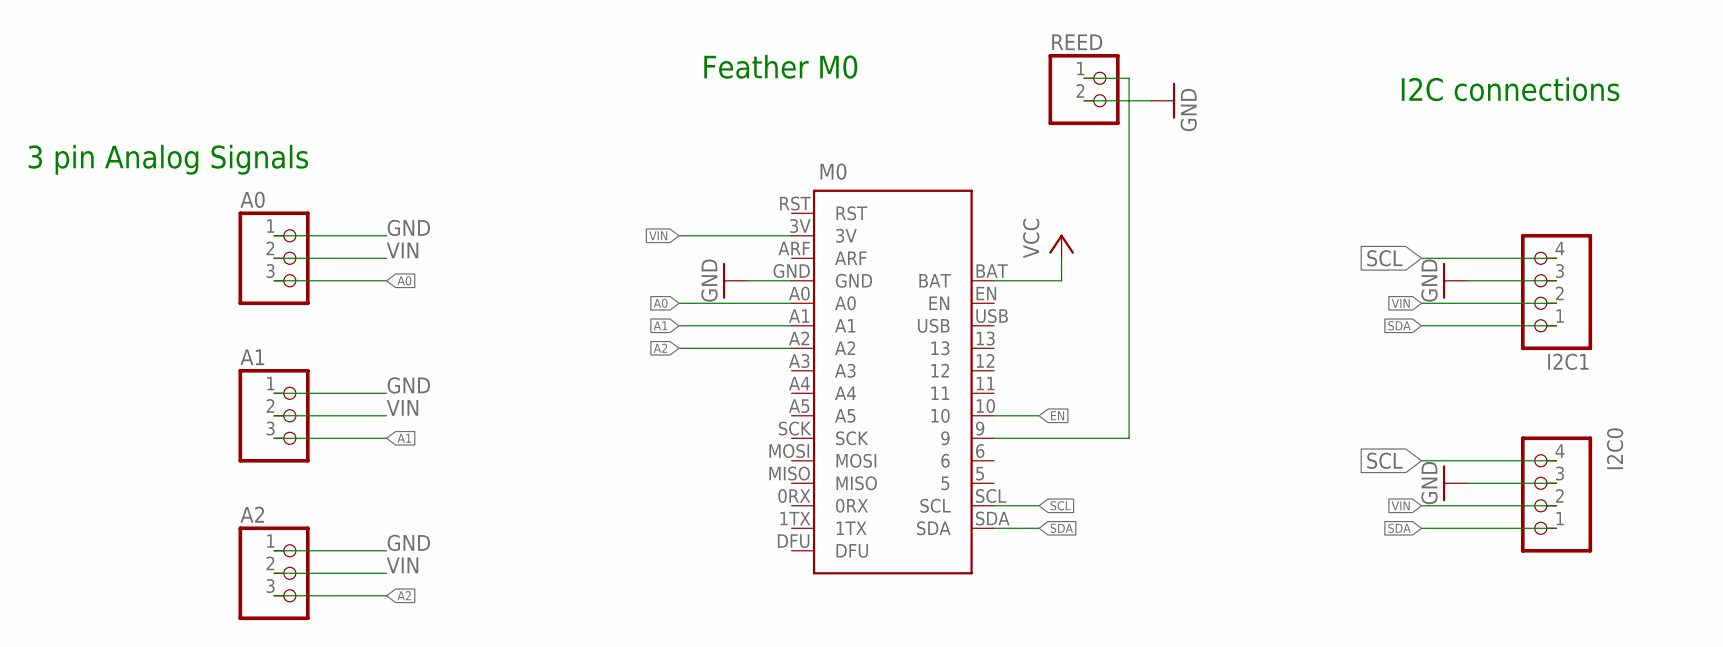
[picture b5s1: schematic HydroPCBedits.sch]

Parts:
A0, A1, A2: PINHD-1X3; 1X03
I2C0, I2C1: PINHD-1X4; 1X04
M0: BLUEFRUIT_M0; BLUEFRUIT_MO
REED: PINHD-1X2; 1X02

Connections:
A0: A0.3, M0.A0
A1: A1.3, M0.A1
A2: A2.3, M0.A2
EN: M0.10
GND: A0.1, A1.1, A2.1, I2C0.3, I2C1.3, M0.GND, REED.2
unnamed: M0.9, REED.1
SCL: I2C0.4, I2C1.4, M0.SCL
SDA: I2C0.1, I2C1.1, M0.SDA
VCC: M0.BAT
VIN: A0.2, A1.2, A2.2, I2C0.2, I2C1.2, M0.3V

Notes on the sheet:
3 pin Analog Signals
I2C connections
Feather M0

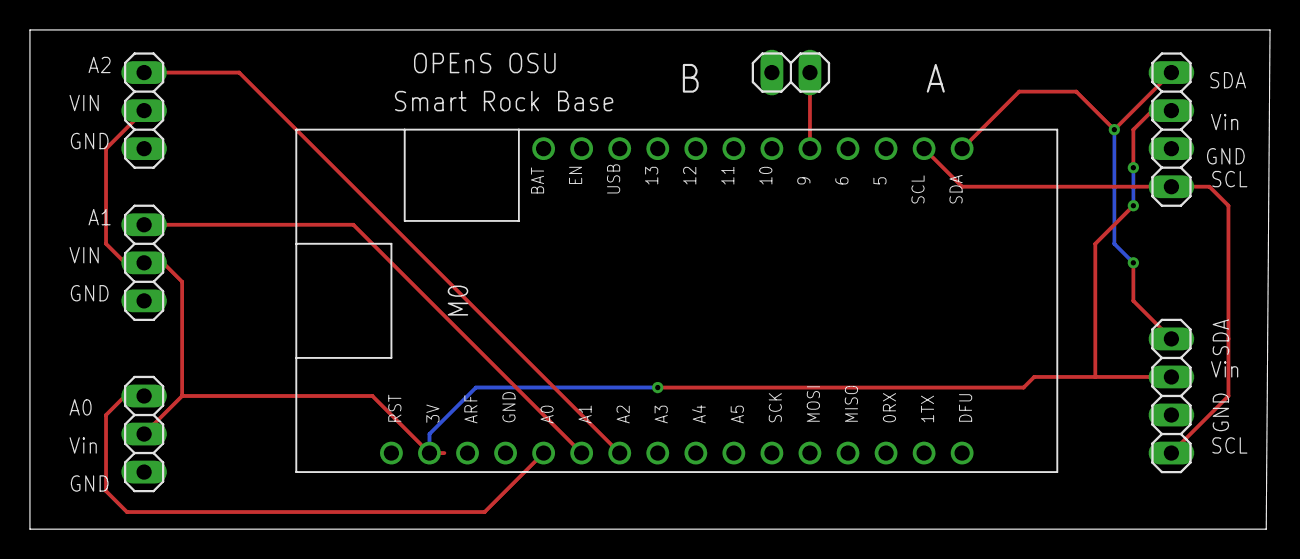
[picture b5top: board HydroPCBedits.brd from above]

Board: 2 copper layers, 82.8 x 33.3 mm, 7 parts (0 on the bottom side), 8 nets.

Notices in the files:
parts and their libraries:
COPYRIGHT: Copyright (C) 2024 Ultra Librarian. All rights reserved.
